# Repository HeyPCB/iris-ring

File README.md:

# Iris Ring

The annular LED board behind each iris of Iris: 12 WS2812-2020 pixels on an 18 mm ring around the camera lens, two per head.

Part of [Iris, the human-eyed robot head](https://github.com/HeyPCB/iris), HeyPCB's open robot boards. Designed end to end with the HeyPCB method on
KiCad 10 (headless pipeline, Freerouting 2.4.1); every number below is measured on the files in this repository.
Mentions of `./run.sh`, `docs/rules/`, `blocks/` or `parts/` refer to the heypcb-kicad SDK that produced them.

| Layers | Outline | Parts | Nets | Connections routed | Vias | ERC errors | DRC errors / unconnected / parity |
|---|---|---|---|---|---|---|---|
| 2 | 18 x 18 mm, shaped with 1 cutout | 30 | 15 | 64 -> 0 open | 10 | 0 | 0 / 0 / 0 |

**Not fabricated, assembled or powered.**

| | |
|---|---|
| KiCad project | [`kicad/`](kicad/) |
| Gerbers (unzipped and zipped), BOM, CPL, STEP, schematic PDF | [`fab/`](fab/) |
| Mechanism CAD, fit check and system docs | [Iris, the human-eyed robot head](https://github.com/HeyPCB/iris) |
| Renders | [top](media/top.png), [bottom](media/bottom.png) |
| Design process, every step as KiCad rendered it | [`media/design-process.mp4`](media/design-process.mp4) |

Iris Ring is the annular LED board that glows behind each iris of **Iris**, an open-hardware robot
head with human eyes. Each head carries two identical boards, one per eye. Each is an 18 mm disc with
a key flat and a 7.6 mm hole for the camera lens, and it carries twelve WS2812C-2020 RGB LEDs. It was
designed with the HeyPCB method on KiCad 10 (the headless heypcb-kicad pipeline, KiCad 10.0.6,
routed by Freerouting 2.4.1). The brief, `board.json`, is written by `make_brief.py` and follows
section 4.4 (B3) and section 5 (interconnect contracts) of the Iris system spec v0.1 (not
published; the contracts are in [the Iris system docs](https://github.com/HeyPCB/iris/blob/main/docs/system.md)).

**It has not been fabricated, assembled or powered.** Every gate number below comes from the final
run's `report.json` (2026-10-03, `./run.sh --board boards/iris_ring` with media,
from an empty build directory). Copper, pad and position numbers were read from
`kicad/iris_ring.kicad_pcb` with KiCad 10.0.6's pcbnew. Thickness and heights were read
from the solids of `fab/iris_ring.step`. Datasheet facts are cited by page under
*Licence and sources*.

| Front (LED face) | Back (camera side) |
|---|---|
|  |  |

The renders show the LED lands without LED bodies, because KiCad 10.0.6 ships no 3D model for
`LED_WS2812B-2020_PLCC4_2.0x2.0mm`. They also show a 1.6 mm board, not 0.8 mm (see *Check before
ordering*). `draw_map.py` draws the map from the routed board.

## Role in Iris

The ring sits inside each 30 mm eyeball, between the camera and the translucent iris disc. It lights
the iris from behind for gaze and mood cues. B1 Cortex drives it from its RMT peripheral (GPIO47 and
GPIO48, 800 kHz, spec section 8) through a 74AHCT1G125 at 5 V.

**Eye stack-up** along the optical axis, x from the eye centre (spec section 2.2; design values, not
measured on hardware):

| x (mm) | Part |
|---|---|
| 4.36 to 7.01 | OV2640 camera module (right eye) or dummy carrier (left eye); the ring's back rests on the holder top |
| **7.0 to 7.8** | **Iris Ring**: back face 7.0, front face 7.8 (0.8 mm board) |
| 7.8 to 8.64 | WS2812C-2020 bodies, 0.84 mm (catalogue row) |
| 7.01 to 9.01 | camera lens barrel, Ø7.2, through the ring's Ø7.6 hole |
| 9.01 to 9.90 | lens front step, Ø5.4, inside the black pupil sleeve (ID 5.6) |
| 8.65 to 11.1 | light-mixing cavity, painted white inside |
| 11.1 to 11.9 | translucent iris disc, Ø14.6, pupil hole Ø5.6 |
| up to 16.40 | clear cornea dome (apex) |

**Orientation in the head.** The board frame used below has its origin at the ring centre, +x away
from the wire pads and +y toward the key flat, seen from the front.
- **Right eye:** +x is +Y_eye (robot-left, the nasal side), +y is -Z_eye (down). The pads are temporal and the flat is down.
- **Left eye:** the same board turned 180° about the optical axis. +x is -Y_eye, +y is +Z_eye: the pads are again temporal, and the flat is up.

## Features

- **Outline as built** (read from Edge.Cuts):
  - a Ø18.000 mm circle drawn as four true arcs of radius 9.000 mm, plus a key flat: the chord 8.400 mm from the centre, 6.462 mm long, ending at (±3.231, 8.400);
  - a Ø7.600 mm centre hole;
  - bounding box 18.0 x 17.4 mm.

  The polygon's corners are where tangents of the circle meet, so their 9 mm fillets are exact arcs and nothing is faceted.
- **2 layers, 0.8 mm (an order option; see *Check before ordering*).** GND is poured on both faces after routing measured 0 open.
- **12 x Worldsemi WS2812C-2020-V1** (C2976072) on the front on r = 6.600 mm, every 30° from 15°, data chained clockwise.
- **One 100 nF per LED** (12 x 0402, C1525) on the back, plus **4.7 uF bulk** (0402, C23733) and a **33 ohm** DIN series resistor (0402, C25105).
- **Four 1.0 mm wire pads** on the back, at the temporal edge, for the RING harness (P1 5V_LED, P2 LED_DIN, P3 GND, P4 GND).
- **No parts in the back's centre 8.7 x 8.7 mm square**, where the board rests on the camera holder (a footprint keepout on B.Cu, spec 4.4). Tracks and vias may pass under it.
- **Heights.**
  - Front: the LED bodies are 0.84 mm (catalogue row), against the spec's 0.9 mm.
  - Back: the 0402 bodies end 0.585 mm below the back face in the fab STEP (KiCad's stock 0402 models), against the spec's 0.6 mm. Add the solder joints of the wires.
- **No holes.** The carrier's seat and the iris disc's rim clamp the board, and the flat keys its rotation.

## LED chain and data direction

```
P2 LED_DIN -> R1 33 ohm -> D1 -> D2 -> D3 -> ... -> D11 -> D12      (D12 DOUT is not connected)
```

- **Seen from the front, the chain runs clockwise** in both eyes. It starts at D1, the first LED clockwise after the wire pads, and ends at D12, the last LED before them.
  - Right eye: D1 sits on the temporal side, 15° above horizontal.
  - Left eye (board turned 180°): D1 sits on the temporal side, 15° below horizontal.
- **Firmware index k-1 is LED Dk.** A frame is 12 x 24 bits in GRB order, most significant bit first, at 800 kbit/s: 360 µs, then more than 280 µs low to latch (datasheet p.4).
- **Data hops** (front copper, measured): DIN2 to DIN12 repeat 3.04, 1.91 and 3.43 mm four times, one for each quarter of the ring. DIN1 runs from R1 on the back through one via to D1: 2.86 mm on B.Cu and 1.37 mm on F.Cu.

| LED | Angle | Centre (x, y) mm | LED | Angle | Centre (x, y) mm |
|---|---|---|---|---|---|
| D1 | 195° | (-6.375, -1.708) | D7 | 15° | (6.375, 1.708) |
| D2 | 225° | (-4.667, -4.667) | D8 | 45° | (4.667, 4.667) |
| D3 | 255° | (-1.708, -6.375) | D9 | 75° | (1.708, 6.375) |
| D4 | 285° | (1.708, -6.375) | D10 | 105° | (-1.708, 6.375) |
| D5 | 315° | (4.667, -4.667) | D11 | 135° | (-4.667, 4.667) |
| D6 | 345° | (6.375, -1.708) | D12 | 165° | (-6.375, 1.708) |

Angles are measured from +x toward +y, which is clockwise seen from the front. Every centre is at
r = 6.600 mm.

**LED orientation.** Each LED is turned so that DOUT and GND face the rim and DIN and VDD face the
hole, with DOUT on the clockwise side. Data then hops from one LED's outer DOUT to the next LED's
inner DIN, and no hop crosses a supply connection. The SDK places parts in quarter turns only, so
each LED faces the axis nearest its radius. The four diagonal LEDs (D2, D5, D8, D11) take their
clockwise neighbour's turn. That gives 2.56 and 1.86 mm from DOUT pad centre to DIN pad centre; the
other choice gives 4.00 and 3.33 mm.

## Pinout (spec section 5, binding)

RING_R runs from B1 J2 to the right eye's ring, and RING_L from B1 J3 to the left eye's ring.
Each is a JST SH-4 (SM04B-SRSS-TB) at B1, then four 32 AWG silicone wires, 100 mm, soldered to the
pads below.

| B1 pin | B3 pad | Net | Direction | Level |
|---|---|---|---|---|
| 1 | P1 | 5V_LED | B1 -> B3 | 5V_SYS through a 0.5 A PTC or ferrite on B1 (4.85 V nominal at B1's input); the source is B2, via B1 |
| 2 | P2 | LED_DIN | B1 -> B3 | 5 V CMOS from 74AHCT1G125, WS2812 protocol at 800 kHz |
| 3 | P3 | GND | — | |
| 4 | P4 | GND | — | |

Pad centres on the back, measured, in mm from the ring centre (board frame, as seen from the front):

| Pad | Board (x, y) | Right eye (Y, Z) | Left eye (Y, Z) |
|---|---|---|---|
| P1 5V_LED | (-6.952, -3.070) | (-6.952, +3.070) | (+6.952, -3.070) |
| P2 LED_DIN | (-7.527, -1.050) | (-7.527, +1.050) | (+7.527, -1.050) |
| P3 GND | (-7.527, +1.050) | (-7.527, -1.050) | (+7.527, +1.050) |
| P4 GND | (-6.952, +3.070) | (-6.952, -3.070) | (+6.952, +3.070) |

- All four pads are Ø1.0 mm SMD pads on the back face (x_eye = +7.0), on r = 7.6 mm, 2.1 mm centre to centre.
- In the right eye, P1 is the top pad. In the left eye, P1 is the bottom pad.
- The silkscreen carries no pad names (no room at this pitch); the map above has them.

## LED current and power, per ring

From the WS2812C-2020-V1 datasheet: 5 mA per colour channel (p.1, and the LED test condition on
p.3), and 0.5 mA quiescent per LED (p.3). Power is at 4.85 V, H1's nominal 5V_SYS (spec section 5);
the drop in B1's PTC or ferrite and in the harness is not counted.

| State | Current | Power |
|---|---|---|
| Full white: 12 x (3 x 5 mA + 0.5 mA) | 186 mA | 0.90 W |
| Firmware cap, 30 % brightness (spec section 8): 0.3 x 180 mA + 6 mA | 60 mA | 0.29 W |
| All dark: 12 x 0.5 mA | 6 mA | 29 mW |
| One LED at full white | 15.5 mA | 75 mW |

- **Per head** (two rings) at full white: 372 mA, 1.80 W. The spec budgets 180 mA per ring and does not count the quiescent current.
- **Supply copper.** 5V_LED is 67.24 mm of 0.3 mm track and 4.23 mm of 0.225 mm track. The import's width floor kept the narrower stretches where 0.3 mm would not clear another net. By IPC-2221 at a 10 °C rise on 1 oz outer copper (`route.ipc2221_amps`), 0.225 mm carries 0.81 A and 0.3 mm carries 1.00 A: four times the full-white current or more.
- **Supply range:** the datasheet gives VDD +3.7 to +5.3 V (p.3, in its Absolute Maximum Ratings table), and VIH 2.7 V minimum at VDD 5 V (p.3).
- **Decoupling path.** Each LED has its own 100 nF on the back, under its inner pads, but Freerouting did not join each pair through its own via:
  - it tied the twelve VDD pads together with a front ring, and the capacitors with a back ring;
  - it joined the two rings with 4 vias;
  - the copper path from each LED's VDD pad to its own capacitor is 4.51 to 13.88 mm long (D8 and D6), measured on the board's track graph.

## Measured gates

| Gate | Result |
|---|---|
| Composition | 13 block instances (12 `irisring_pixel`, 1 `irisring_wire_in`) -> 30 parts, 15 nets, 1 no-connect (D12 DOUT) |
| Part binding (`parts/lcsc_pinned.json`) | 26 of 26 BOM parts bound, 0 unsourced, 0 identity conflicts; the four wire pads are do-not-populate (nothing to buy). 1 distinct Extended part (the LED), about $3 in JLC loading fees |
| ERC (`kicad-cli sch erc --severity-all`) | 0 errors, 0 warnings |
| Netlist round trip | identical, 15 nets |
| Freerouting, rung 1, fanout on (kept) | 64 -> 1 open; the last mile closed it (GND, D10.2 to C1.2, 3.16 mm, no via; kept by DRC): **0 open**, DRC score 0 |
| Freerouting, rung 1, fanout off (measured for comparison) | 64 -> 1 open (DIN11, D10.1 to D11.3); the last mile found no path. DRC score 1 |
| Copper | 225 tracks, 10 vias (5 GND, 4 5V_LED, 1 DIN1), 191.4 mm of track (F.Cu 105.4, B.Cu 86.0). No class was narrowed |
| Pours (only after a measured 0 open) | GND on F.Cu and B.Cu; 0 stitching vias (no point of the 3 mm lattice fitted); 0 open after the pour and at the end; no island-repair vias |
| Silkscreen | the name, "Iris" and "Ring", placed as 2 words on the back; 5 back designators seated (C2, C3, C5, C6, C7), 23 hidden where nothing fit; nothing clipped |
| DRC (`--severity-all --schematic-parity`, KiCad 10.0.6) | fresh, **0 errors, 0 warnings, 0 unconnected, 0 parity** |
| DFM (`jlcpcb_2layer`) | 0 errors, 1 warning (92 stock-footprint silk strokes at 0.12 mm; the fab prints them at its 0.15 mm minimum) |
| Fab gate | **ready**, no blockers; gerbers for 2 copper layers, drill, BOM, JLC CPL (8 rotations corrected), schematic PDF, STEP |
| Media | renders and the design-process video (108.5 s, 158 frames), in `build/iris_ring/` (not committed) |

## Decisions and departures from the spec

| The spec says | On the board | Why |
|---|---|---|
| LEDs on r = 6.6 at 15° + 30°·k | Exactly that, every lock computed from its angle (`make_brief.py`) | Each centre is at r = 6.600 mm (measured) |
| (implied) LEDs turned radially | **Quarter turns**: each LED faces the axis nearest its radius | The SDK places parts at 0, 90, 180 or 270° only. A lock at 225° stops the place stage with an unnamed `ValueError: 225` from `place._rot_pt`. The positions keep 4-fold symmetry, and so do the data hops |
| P1-P4: `Connector_Generic:Conn_01x04` on 4 x `TestPoint_Pad_D1.0mm`, r = 7.35, 1.27 mm pitch | 4 x `Connector:TestPoint` on `TestPoint_Pad_D1.0mm`, on **r = 7.6, 2.1 mm apart** | A 4-pin symbol cannot sit on four 1-pad footprints. The stock footprint's courtyard is a Ø2.0 mm circle, so 1.27 mm pitch is a `courtyards_overlap` DRC error. The pads keep their Ø1.0 mm and the §5 order |
| C1-C12 on the back at r ≥ 6.3 | **8 at r = 5.28** (C1, C3, C4, C6, C7, C9, C10, C12), lying along the ring under their LED's inner pads; **4 at r = 7.40** on the diagonals (C2, C5, C8, C11) | The inner positions leave the back's band above the key flat free for the board's name, and put each capacitor's 5V_LED pad beside its LED's VDD pad. Every part clears the camera-holder square: `make_brief.py` checks it, and the keepout's DRC confirms it. On the diagonals the square's corner reaches r = 6.15, so those four stay outside it |
| Copper to edge: not in the spec (the other boards here use 0.5 mm) | **0.3 mm** | D9 and D10 come to 0.76 mm from the key flat. At 0.5 mm no ground track fitted below them, the router ran GND between the LEDs, and DIN11 stayed open (measured on this brief). At 0.3 mm it routes to 0 open |
| Board name on the back "if it fits" | **"Iris Ring"** as two silk words below C9 and C10, in a via-free window | As a title line it found no room: the silk stage seats designators first, and they took the only free band. Words are placed before designators |

## Assembly notes

- **Two per head, one per eye.** The boards are identical; build four for two heads plus spares.
- **Orientation by the key flat.**
  - The carrier's seat (Ø18.2 x 0.8 with a flat, spec section 7.1, part P4) turns the board.
  - Right eye: flat down, wire pads temporal.
  - Left eye: flat up, wire pads temporal.
  - The LEDs face the iris. The back, with the capacitors and pads, faces the camera.
- **The camera lens passes through the right eye's ring.**
  - The OV2640's Ø7.2 mm lens barrel runs through the Ø7.6 mm hole (spec section 2.2), about 0.2 mm radial clearance by the spec's numbers.
  - The board's back rests on the 8.5 x 8.5 mm holder top, which is why the centre 8.7 mm square of the back carries no parts.
  - The black pupil sleeve (ID 5.6) runs over the lens step inside the hole, so no LED light reaches the lens.
  - The left eye has the dummy carrier with the same envelope and a black pupil plug.
- **Wires.**
  - Solder the four 32 AWG wires to P1-P4 on the back, in the map's order: P1 5V_LED nearest the top in the right eye.
  - Keep each joint inside the back's 0.6 mm height budget, and lead the wires into the carrier's wire channel.
  - B1's J2 and J3 are interchangeable by design; firmware has a swap flag (spec section 5).
- **Clamp.**
  - The LED bodies reach r = 8.09 mm on the diagonals and 7.95 mm elsewhere (KiCad's 2.2 x 2.0 mm F.Fab outline).
  - The iris disc's clamping rim must land on the front between r = 8.1 and the 9.0 mm edge, or on the flat.
- **LED handling** (datasheet):
  - Moisture level 5a: 24 h out of the bag at under 30 °C and 60 % RH, else bake at 75 °C for more than 24 h (p.7-8).
  - Reflow peak 245 °C (p.8).
  - The parts are on both faces: 12 LEDs on the top, 14 parts on the bottom (CPL).
- **First test.** Light D1 to D12 in turn: D1 must be the first LED clockwise after the pads, seen from the front.

## Check before ordering

- **Order 0.8 mm thickness.**
  - The pipeline has no thickness setting. Its gerber job states `BoardThickness` 1.6 mm (KiCad's default 2-layer stackup: 0.035 mm copper, 1.51 mm FR4).
  - The fab STEP's board body is 1.510 mm thick (z 0 to 1.510, measured on the solid), and the renders show the same.
  - Choose 0.8 mm in the fab's order form. The eye stack-up above assumes 0.8 mm: at 1.6 mm the LEDs would stand 0.8 mm further into the light-mixing cavity.
  - The mechanism's fit check against this board's STEP confirms it ([`cad/out/fit.json`](https://github.com/HeyPCB/iris/blob/main/cad/out/fit.json), board B3): at 0.8 mm the ring seats in the eye carrier under the iris clamp ring with no collision; at the exported 1.51 mm the board overlaps the clamp ring by 21.3 mm³, so the clamp would sit 0.71 mm high.
- **0.3 mm copper to edge.** Confirm it against the fab's routed-edge rule; the other boards in this repository use 0.5 mm.
- **Mechanism CAD.**
  - Use the outline and pad positions above, and the wire-pad pitch of 2.1 mm, not the spec's 1.27 mm.
  - The fab STEP has **no LED bodies** (no KiCad model). Add 2.2 x 2.0 x 0.84 mm envelopes (the catalogue row; KiCad's F.Fab outline is 2.2 x 2.0) at the LED centres in the table, turned as on the map.
  - Back-side capacitors sit at r = 5.28 and 7.40 mm. They need the carrier's 0.6 mm relief there, outside the holder's square.
- **The 4.7 uF's height.** The STEP uses KiCad's generic 0402 model (0.5 mm body). Confirm CL05A475MP5NRNC's thickness on its datasheet: the back's budget is 0.6 mm.
- **Bulk capacitance at 5 V.** CL05A475MP5NRNC is a 10 V X5R part. Its capacitance at 5 V bias is below 4.7 uF (not measured here).
- **LED rotation in the assembler's preview.** The pipeline's JLC CPL corrected 8 rotations. Check that each LED's pin-1 chamfer matches the silkscreen: a part turned 180° swaps VDD with GND.
- **Stock.** Live lookups of 2026-10-03: C2976072 376,897 (Extended); C25105 968,914; C23733 964,426. C1525 had 16,407,331 at its 2026-09-30 snapshot. Re-check on the day.
- **Decoupling path.** If a scope shows supply noise at an LED, the 13.88 mm path from D6 to its C6 is the longest (see *LED current and power*).
- **Silkscreen.** Five back designators printed and the rest did not; the wire-pad names are only on the map.

## Files

- `board.json`: the brief, written by `make_brief.py`. Edit the script, not the JSON. The script places every part by formula and checks courtyards, the camera-holder square and the edge clearances before the pipeline runs.
- `make_brief.py`: the outline, every lock and the brief (Python 3.9+, standard library only).
- `draw_map.py`: the assembly map, `img/iris_ring_map.svg`, drawn from the routed board (run it under KiCad's Python).
- `img/`: KiCad's raytraced renders of both faces and an angled view (`iris_ring_3d.jpg`), and the map.
- Blocks: `blocks/irisring_pixel.json` (one LED and its 100 nF) and `blocks/irisring_wire_in.json` (wire pads, 33 ohm, 4.7 uF).
- Part rows: C2976072, C25105 and C23733 in `parts/lcsc_pinned.json`, from live lookups of 2026-10-03.
- Regenerate everything with `python3 boards/iris_ring/make_brief.py`, then `./run.sh --board boards/iris_ring`. The outputs land in `build/iris_ring/`, which is not committed: gerbers, drill, BOM, CPL, schematic PDF and STEP in `fab/`, and the renders and video.

## Licence and sources

The Iris Ring design files are licensed under the **CERN Open Hardware Licence Version 2 -
Strongly Reciprocal (CERN-OHL-S-2.0)**, https://ohwr.org/cern_ohl_s_v2.txt. They are this
directory, `blocks/irisring_pixel.json` and `blocks/irisring_wire_in.json`. KiCad's symbols,
footprints and 3D models are CC-BY-SA-4.0 with the KiCad library exception. No datasheet is copied
into this repository.

- Worldsemi WS2812C-2020-V1 datasheet (V1.0, 2021-06-24), via LCSC, https://www.lcsc.com/datasheet/C2976072.pdf:
  - p.1: 5 mA per colour channel; 800 kbit/s;
  - p.2: pins 1 DO, 2 GND, 3 DI, 4 VDD, which matches KiCad's `LED:WS2812B-2020` symbol (1 DOUT, 2 VSS, 3 DIN, 4 VDD);
  - p.3: VDD +3.7 to +5.3 V, VIH 2.7 V min, VIL 0.7 V max, quiescent current 0.5 mA, luminous intensity at 5 mA (R 100-150, G 250-400, B 45-75 mcd);
  - p.4: GRB bit order and reset time above 280 µs;
  - p.5: 100 nF across VDD per LED;
  - p.7-8: moisture level 5a and the 245 °C reflow peak.
- LCSC C2976072 product page, https://www.lcsc.com/product-detail/C2976072.html: 0.84 mm body height (the catalogue row read on 2026-10-03).
- Iris system spec v0.1 (not published), sections 2.2, 4.4, 4.5, 5, 6 and 8; its binding contracts are in [the Iris system docs](https://github.com/HeyPCB/iris/blob/main/docs/system.md).

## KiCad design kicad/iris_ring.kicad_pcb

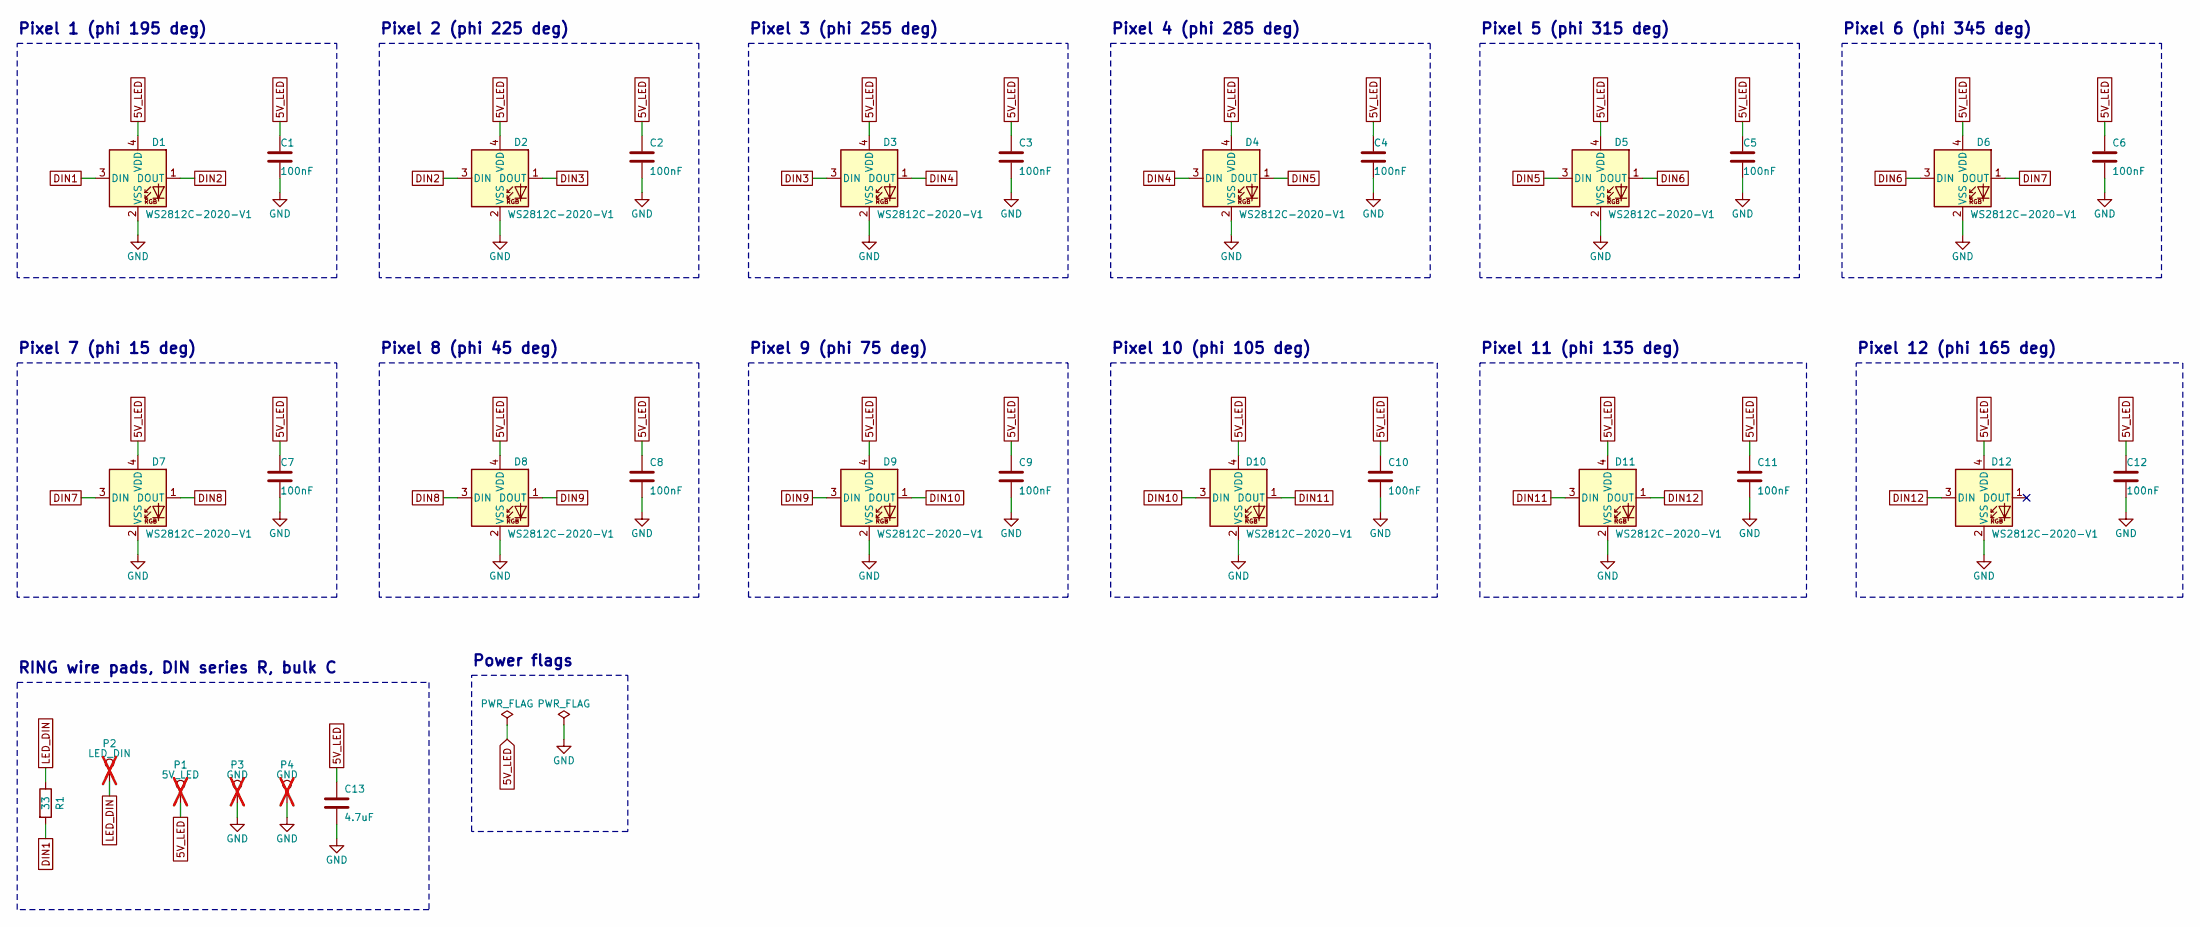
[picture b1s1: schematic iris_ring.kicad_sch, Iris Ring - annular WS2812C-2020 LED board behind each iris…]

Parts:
C1, C2, C3, C4, C5, C6, C7, C8, C9, C10, C11, C12: 100nF; C_0402_1005Metric; MPN CL05B104KO5NNNC; LCSC C1525
C13: 4.7uF; C_0402_1005Metric; MPN CL05A475MP5NRNC; LCSC C23733
D1, D2, D3, D4, D5, D6, D7, D8, D9, D10, D11, D12: WS2812C-2020-V1; LED_WS2812B-2020_PLCC4_2.0x2.0mm; MPN WS2812C-2020-V1; LCSC C2976072
P1: 5V_LED; TestPoint_Pad_D1.0mm; not fitted
P2: LED_DIN; TestPoint_Pad_D1.0mm; not fitted
P3, P4: GND; TestPoint_Pad_D1.0mm; not fitted
R1: 33; R_0402_1005Metric; MPN 0402WGF330JTCE; LCSC C25105

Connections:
5V_LED: C1.1, C2.1, C3.1, C4.1, C5.1, C6.1, C7.1, C8.1, C9.1, C10.1, C11.1, C12.1, C13.1, D1.4 (VDD), D2.4 (VDD), D3.4 (VDD), D4.4 (VDD), D5.4 (VDD), D6.4 (VDD), D7.4 (VDD), D8.4 (VDD), D9.4 (VDD), D10.4 (VDD), D11.4 (VDD), D12.4 (VDD), P1.1
DIN1: D1.3 (DIN), R1.2
DIN2: D1.1 (DOUT), D2.3 (DIN)
DIN3: D2.1 (DOUT), D3.3 (DIN)
DIN4: D3.1 (DOUT), D4.3 (DIN)
DIN5: D4.1 (DOUT), D5.3 (DIN)
DIN6: D5.1 (DOUT), D6.3 (DIN)
DIN7: D6.1 (DOUT), D7.3 (DIN)
DIN8: D7.1 (DOUT), D8.3 (DIN)
DIN9: D8.1 (DOUT), D9.3 (DIN)
DIN10: D9.1 (DOUT), D10.3 (DIN)
DIN11: D10.1 (DOUT), D11.3 (DIN)
DIN12: D11.1 (DOUT), D12.3 (DIN)
GND: C1.2, C2.2, C3.2, C4.2, C5.2, C6.2, C7.2, C8.2, C9.2, C10.2, C11.2, C12.2, C13.2, D1.2 (VSS), D2.2 (VSS), D3.2 (VSS), D4.2 (VSS), D5.2 (VSS), D6.2 (VSS), D7.2 (VSS), D8.2 (VSS), D9.2 (VSS), D10.2 (VSS), D11.2 (VSS), D12.2 (VSS), P3.1, P4.1
LED_DIN: P2.1, R1.1

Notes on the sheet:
Pixel 1 (phi 195 deg)
Pixel 2 (phi 225 deg)
Pixel 3 (phi 255 deg)
Pixel 4 (phi 285 deg)
Pixel 5 (phi 315 deg)
Pixel 6 (phi 345 deg)
Pixel 7 (phi 15 deg)
Pixel 8 (phi 45 deg)
Pixel 9 (phi 75 deg)
Pixel 10 (phi 105 deg)
Pixel 11 (phi 135 deg)
Pixel 12 (phi 165 deg)
RING wire pads, DIN series R, bulk C
Power flags

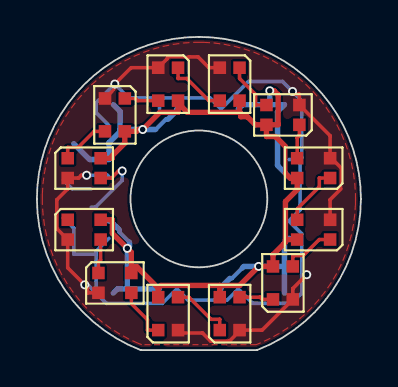
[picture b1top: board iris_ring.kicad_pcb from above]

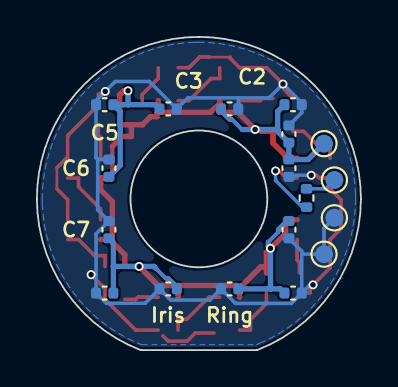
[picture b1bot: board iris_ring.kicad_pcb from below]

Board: 2 copper layers, 18.0 x 17.4 mm, 30 parts (18 on the bottom side), 15 nets.

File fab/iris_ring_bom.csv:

"Reference","Value","Footprint","MPN","LCSC","Qty"
"C1,C2,C3,C4,C5,C6,C7,C8,C9,C10,C11,C12","100nF","Capacitor_SMD:C_0402_1005Metric","CL05B104KO5NNNC","C1525","12"
"C13","4.7uF","Capacitor_SMD:C_0402_1005Metric","CL05A475MP5NRNC","C23733","1"
"D1,D2,D3,D4,D5,D6,D7,D8,D9,D10,D11,D12","WS2812C-2020-V1","LED_SMD:LED_WS2812B-2020_PLCC4_2.0x2.0mm","WS2812C-2020-V1","C2976072","12"
"R1","33","Resistor_SMD:R_0402_1005Metric","0402WGF330JTCE","C25105","1"
